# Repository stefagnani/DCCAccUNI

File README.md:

# DCCAccUNI
Decoder DCC accessori universale. Più versioni basati su hardware di base simile per più funzioni

DECODER ACCESSORI UNIVERSALE

Basato su Software e hardware di MERG
https://www.merg.org.uk/resources/dcc_download

Il presente progetto illustra la realizzazione di un decoder DCC accesori per pilotare in alternativa 4 motori lenti (tipo Tortoise Conrad, o KATO)  4 motori elettromeganertici oppure otto luci generiche per illuminazione o segnali.

Basato sul software originale di MERG versione ACC5, permette un funzionamento toggle standard come da specifiche DCC, ovvero un unico indirizzo pilota 4 coppie di comandi (due per scambio), oppure può essere configurato per operare singolarmente ogni uscita.

Il progetto comprende N Assy (versioni hardware) delle schede in funzione del tipo di accessori da pilotare. Ad oggi sono previste tre tipologie di Assy:

ASSY #260324             Hardware per pilotare 4 motori elettromagnetici
ASSY#XXXXX		Hardware per pilotare segnali 
ASSY#XXXXX		Harware per pilotare motori lenti di tpo Totroise, KATO ecc.

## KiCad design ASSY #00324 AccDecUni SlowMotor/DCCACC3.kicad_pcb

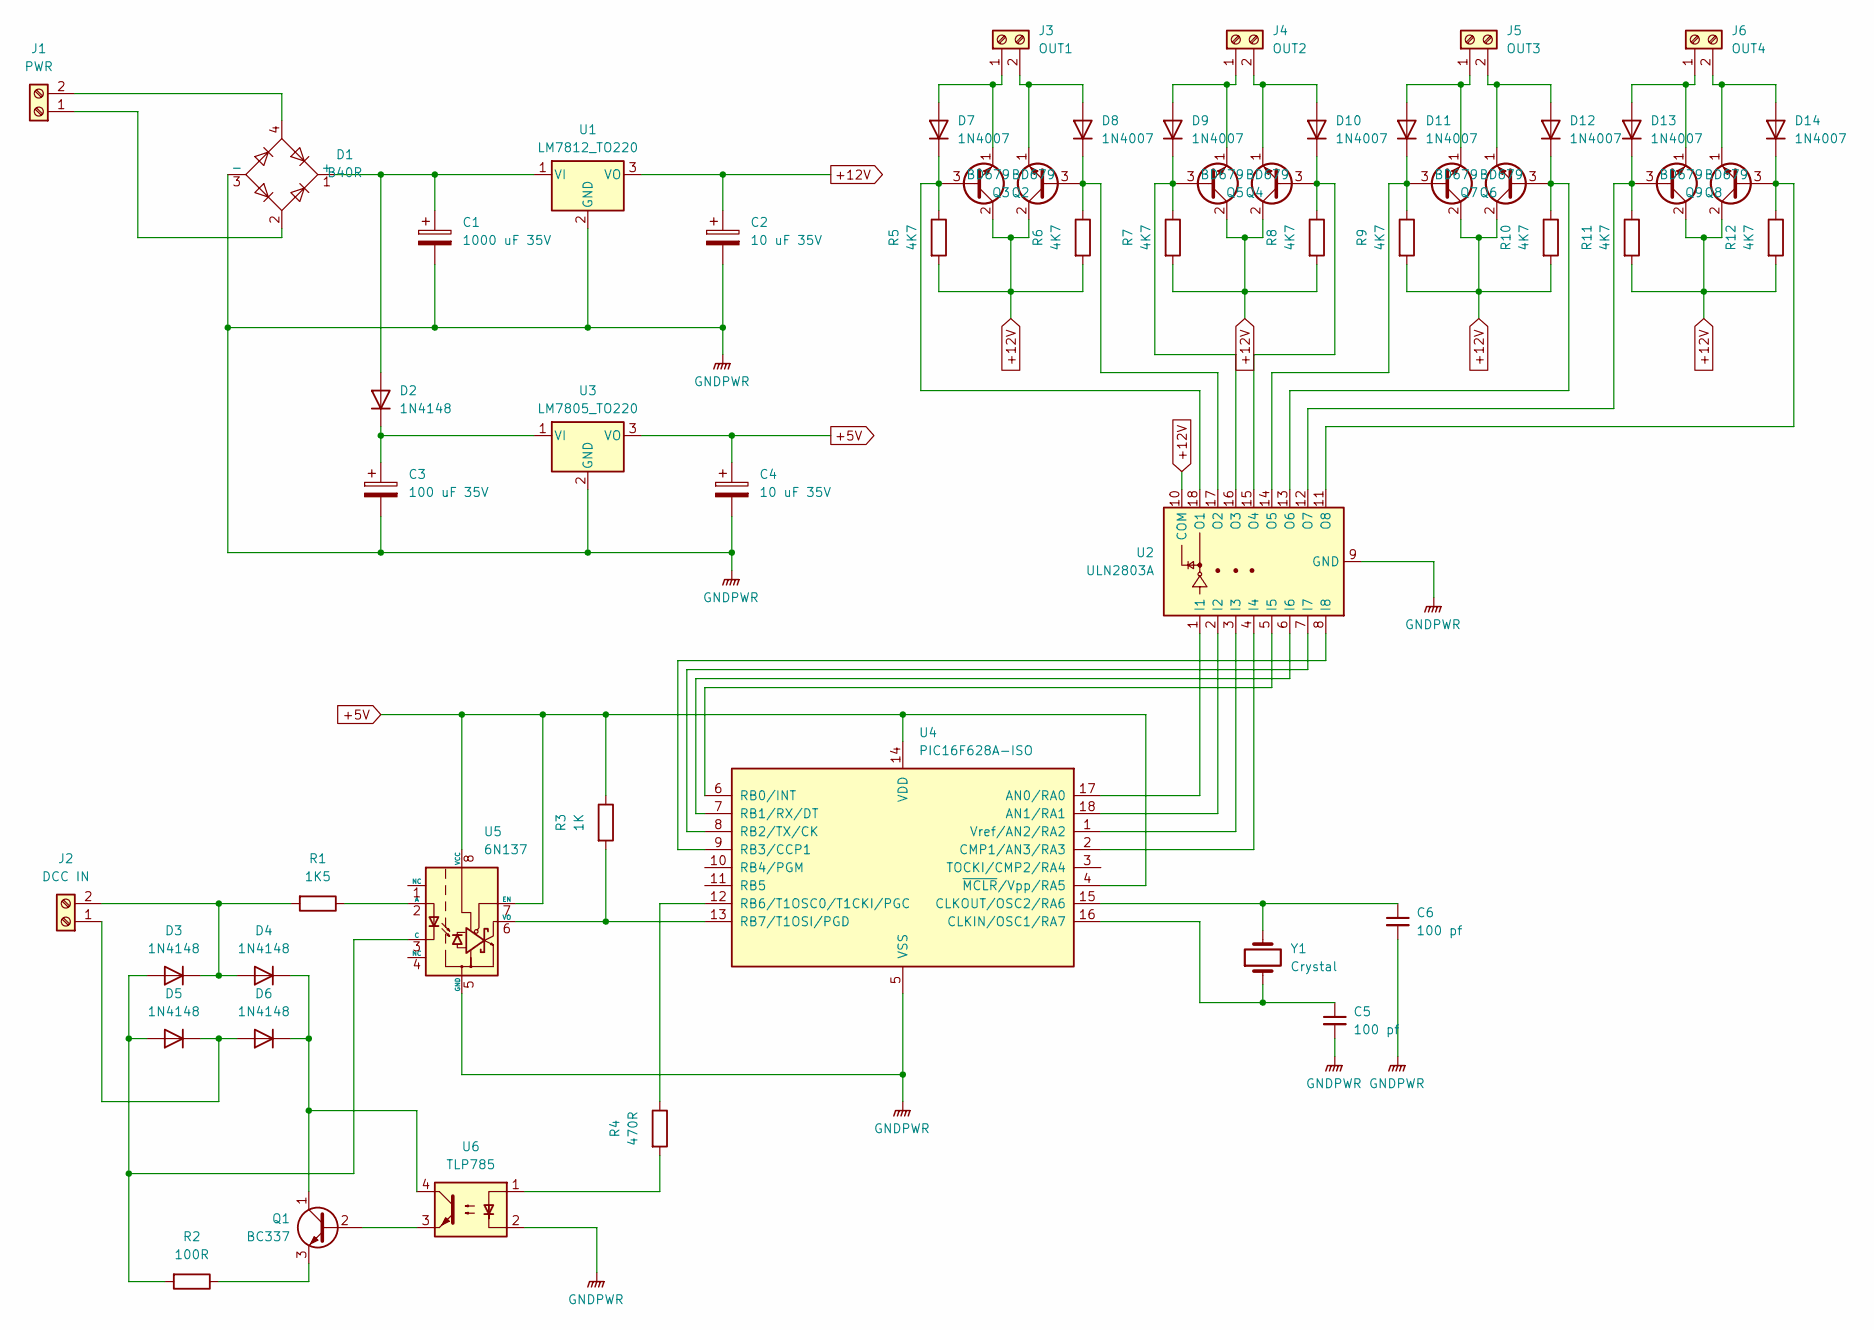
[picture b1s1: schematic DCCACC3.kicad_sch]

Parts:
C1: 1000 uF 35V; CP_Radial_D16.0mm_P7.50mm
C2, C4: 10 uF 35V; CP_Radial_D5.0mm_P2.50mm
C3: 100 uF 35V; CP_Radial_D10.0mm_P5.00mm
C5, C6: 100 pf; C_Disc_D3.0mm_W2.0mm_P2.50mm
D1: B40R; Diode_Bridge_Round_D9.0mm
D2, D3, D4, D5, D6: 1N4148; D_DO-35_SOD27_P7.62mm_Horizontal
D7, D8, D9, D10, D11, D12, D13, D14: 1N4007; D_DO-41_SOD81_P10.16mm_Horizontal
J1: PWR; mkds_1,5-2
J2: DCC IN; mkds_1,5-2
J3: OUT1; mkds_1,5-2
J4: OUT2; mkds_1,5-2
J5: OUT3; mkds_1,5-2
J6: OUT4; mkds_1,5-2
Q1: BC337; TO-92_Inline
Q2, Q3, Q4, Q5, Q6, Q7, Q8, Q9: BD679; TO-126-3_Vertical
R1: 1K5; R_Axial_DIN0207_L6.3mm_D2.5mm_P7.62mm_Horizontal
R2: 100R; R_Axial_DIN0207_L6.3mm_D2.5mm_P7.62mm_Horizontal
R3: 1K; R_Axial_DIN0207_L6.3mm_D2.5mm_P7.62mm_Horizontal
R4: 470R; R_Axial_DIN0207_L6.3mm_D2.5mm_P7.62mm_Horizontal
R5, R6, R7, R8, R9, R10, R11, R12: 4K7; R_Axial_DIN0207_L6.3mm_D2.5mm_P7.62mm_Horizontal
U1: LM7812_TO220; TO-220-3_Vertical
U2: ULN2803A; DIP-18_W7.62mm
U3: LM7805_TO220; TO-220-3_Vertical
U4: PIC16F628A-ISO; DIP-18_W7.62mm
U5: 6N137; DIP-8_W7.62mm
U6: TLP785; DIP-4_W7.62mm
Y1: Crystal; Crystal_HC18-U_Vertical

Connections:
+5V: C4.1, R3.1, U3.3 (VO), U4.4 (~MCLR/Vpp/RA5), U4.14 (VDD), U5.7 (EN), U5.8 (VCC)
+12V: C2.1, Q2.2 (C), Q3.2 (C), Q4.2 (C), Q5.2 (C), Q6.2 (C), Q7.2 (C), Q8.2 (C), Q9.2 (C), R5.2, R6.2, R7.2, R8.2, R9.2, R10.2, R11.2, R12.2, U1.3 (VO), U2.10 (COM)
GNDPWR: C1.2, C2.2, C3.2, C4.2, C5.2, C6.2, D1.3 (-), U1.2 (GND), U2.9 (GND), U3.2 (GND), U4.5 (VSS), U5.5 (GND), U6.2
unnamed: C1.1, D1.1 (+), D2.2 (A), U1.1 (VI)
unnamed: C3.1, D2.1 (K), U3.1 (VI)
unnamed: D3.2 (A), D5.2 (A), R2.2, U5.3 (C)
unnamed: D3.1 (K), D4.2 (A), J2.2, R1.2
unnamed: D4.1 (K), D6.1 (K), Q1.1 (C), U6.4
unnamed: D5.1 (K), D6.2 (A), J2.1
unnamed: D7.2 (A), J3.1, Q2.1 (E)
unnamed: D7.1 (K), Q2.3 (B), R5.1, U2.18 (O1)
unnamed: D8.2 (A), J3.2, Q3.1 (E)
unnamed: D8.1 (K), Q3.3 (B), R6.1, U2.17 (O2)
unnamed: D9.2 (A), J4.1, Q4.1 (E)
unnamed: D9.1 (K), Q4.3 (B), R7.1, U2.16 (O3)
unnamed: D10.2 (A), J4.2, Q5.1 (E)
unnamed: D10.1 (K), Q5.3 (B), R8.1, U2.15 (O4)
unnamed: D11.2 (A), J5.1, Q6.1 (E)
unnamed: D11.1 (K), Q6.3 (B), R9.1, U2.14 (O5)
unnamed: D12.2 (A), J5.2, Q7.1 (E)
unnamed: D12.1 (K), Q7.3 (B), R10.1, U2.13 (O6)
unnamed: D13.2 (A), J6.1, Q8.1 (E)
unnamed: D13.1 (K), Q8.3 (B), R11.1, U2.12 (O7)
unnamed: D14.2 (A), J6.2, Q9.1 (E)
unnamed: D14.1 (K), Q9.3 (B), R12.1, U2.11 (O8)
unnamed: D1.2, J1.1
unnamed: D1.4, J1.2
unnamed: Q1.2 (B), U6.3
unnamed: Q1.3 (E), R2.1
unnamed: R4.2, U6.1
unnamed: U2.1 (I1), U4.17 (AN0/RA0)
unnamed: U2.2 (I2), U4.18 (AN1/RA1)
unnamed: U2.3 (I3), U4.1 (Vref/AN2/RA2)
unnamed: U2.4 (I4), U4.2 (CMP1/AN3/RA3)
unnamed: U2.5 (I5), U4.6 (RB0/INT)
unnamed: U2.6 (I6), U4.7 (RB1/RX/DT)
unnamed: U2.7 (I7), U4.8 (RB2/TX/CK)
unnamed: U2.8 (I8), U4.9 (RB3/CCP1)
unnamed: C5.1, U4.16 (CLKIN/OSC1/RA7), Y1.1
unnamed: C6.1, U4.15 (CLKOUT/OSC2/RA6), Y1.2
unnamed: R4.1, U4.12 (RB6/T1OSC0/T1CKI/PGC)
unnamed: R3.2, U4.13 (RB7/T1OSI/PGD), U5.6 (VO)
unnamed: R1.1, U5.2 (A)

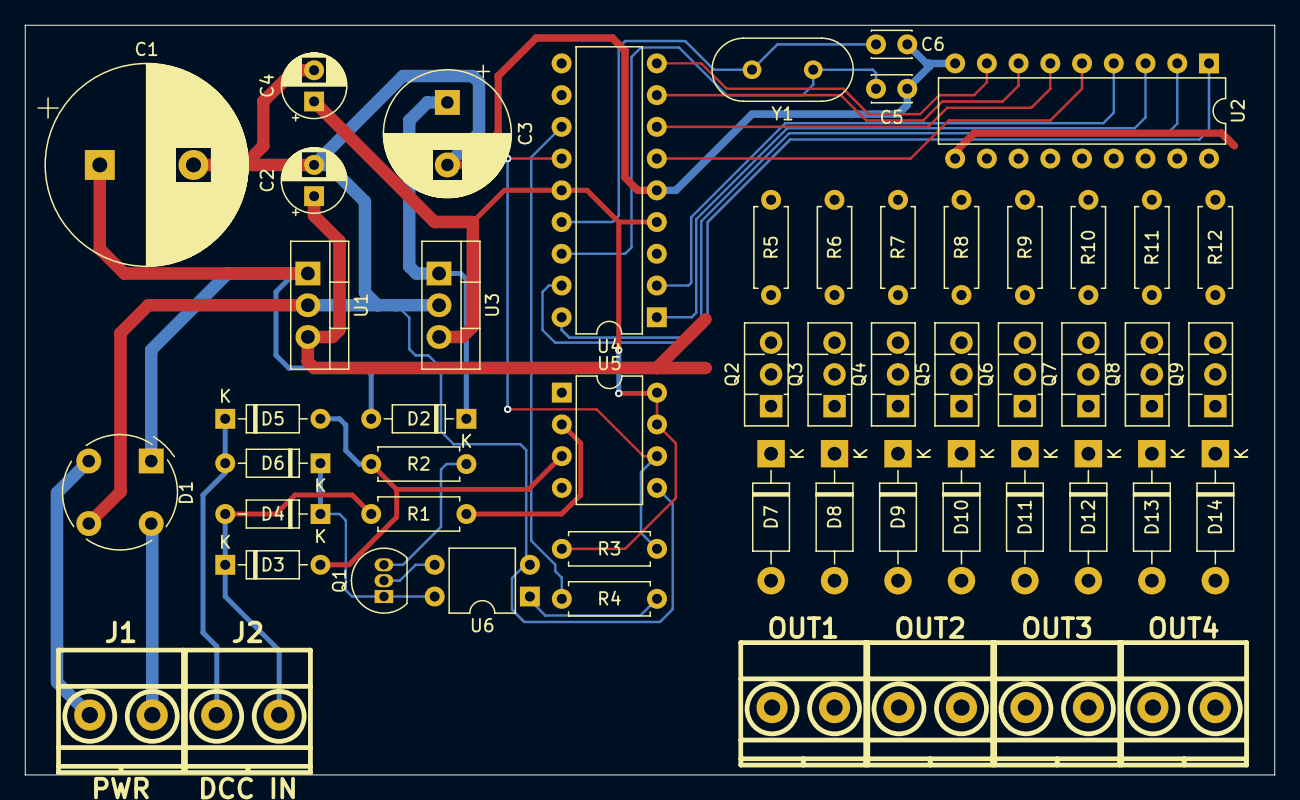
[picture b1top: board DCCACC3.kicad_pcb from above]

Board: 2 copper layers, 100.0 x 60.0 mm, 54 parts (0 on the bottom side), 43 nets.
